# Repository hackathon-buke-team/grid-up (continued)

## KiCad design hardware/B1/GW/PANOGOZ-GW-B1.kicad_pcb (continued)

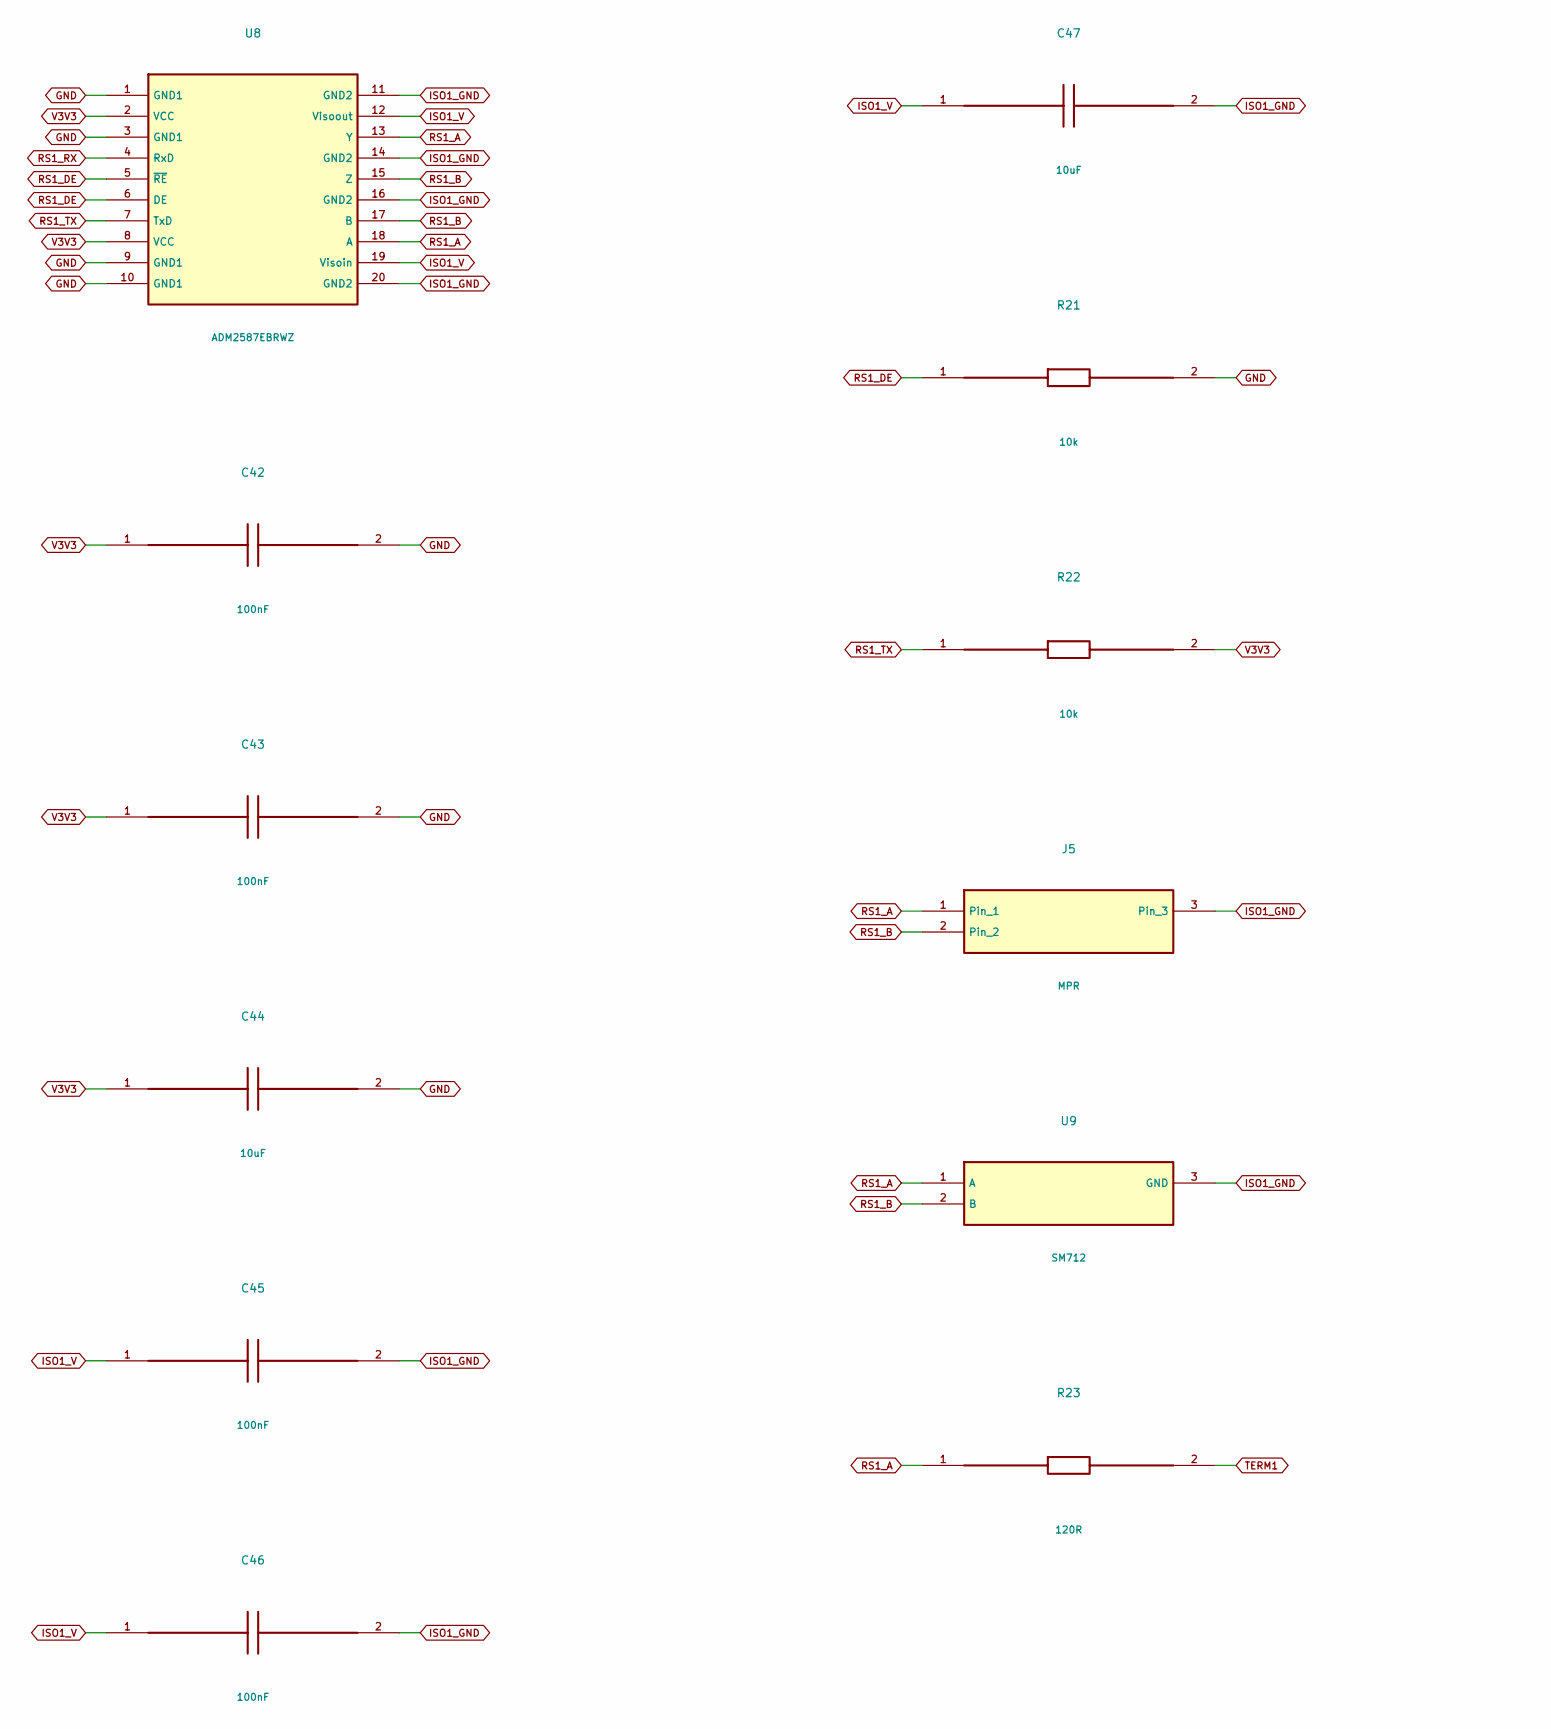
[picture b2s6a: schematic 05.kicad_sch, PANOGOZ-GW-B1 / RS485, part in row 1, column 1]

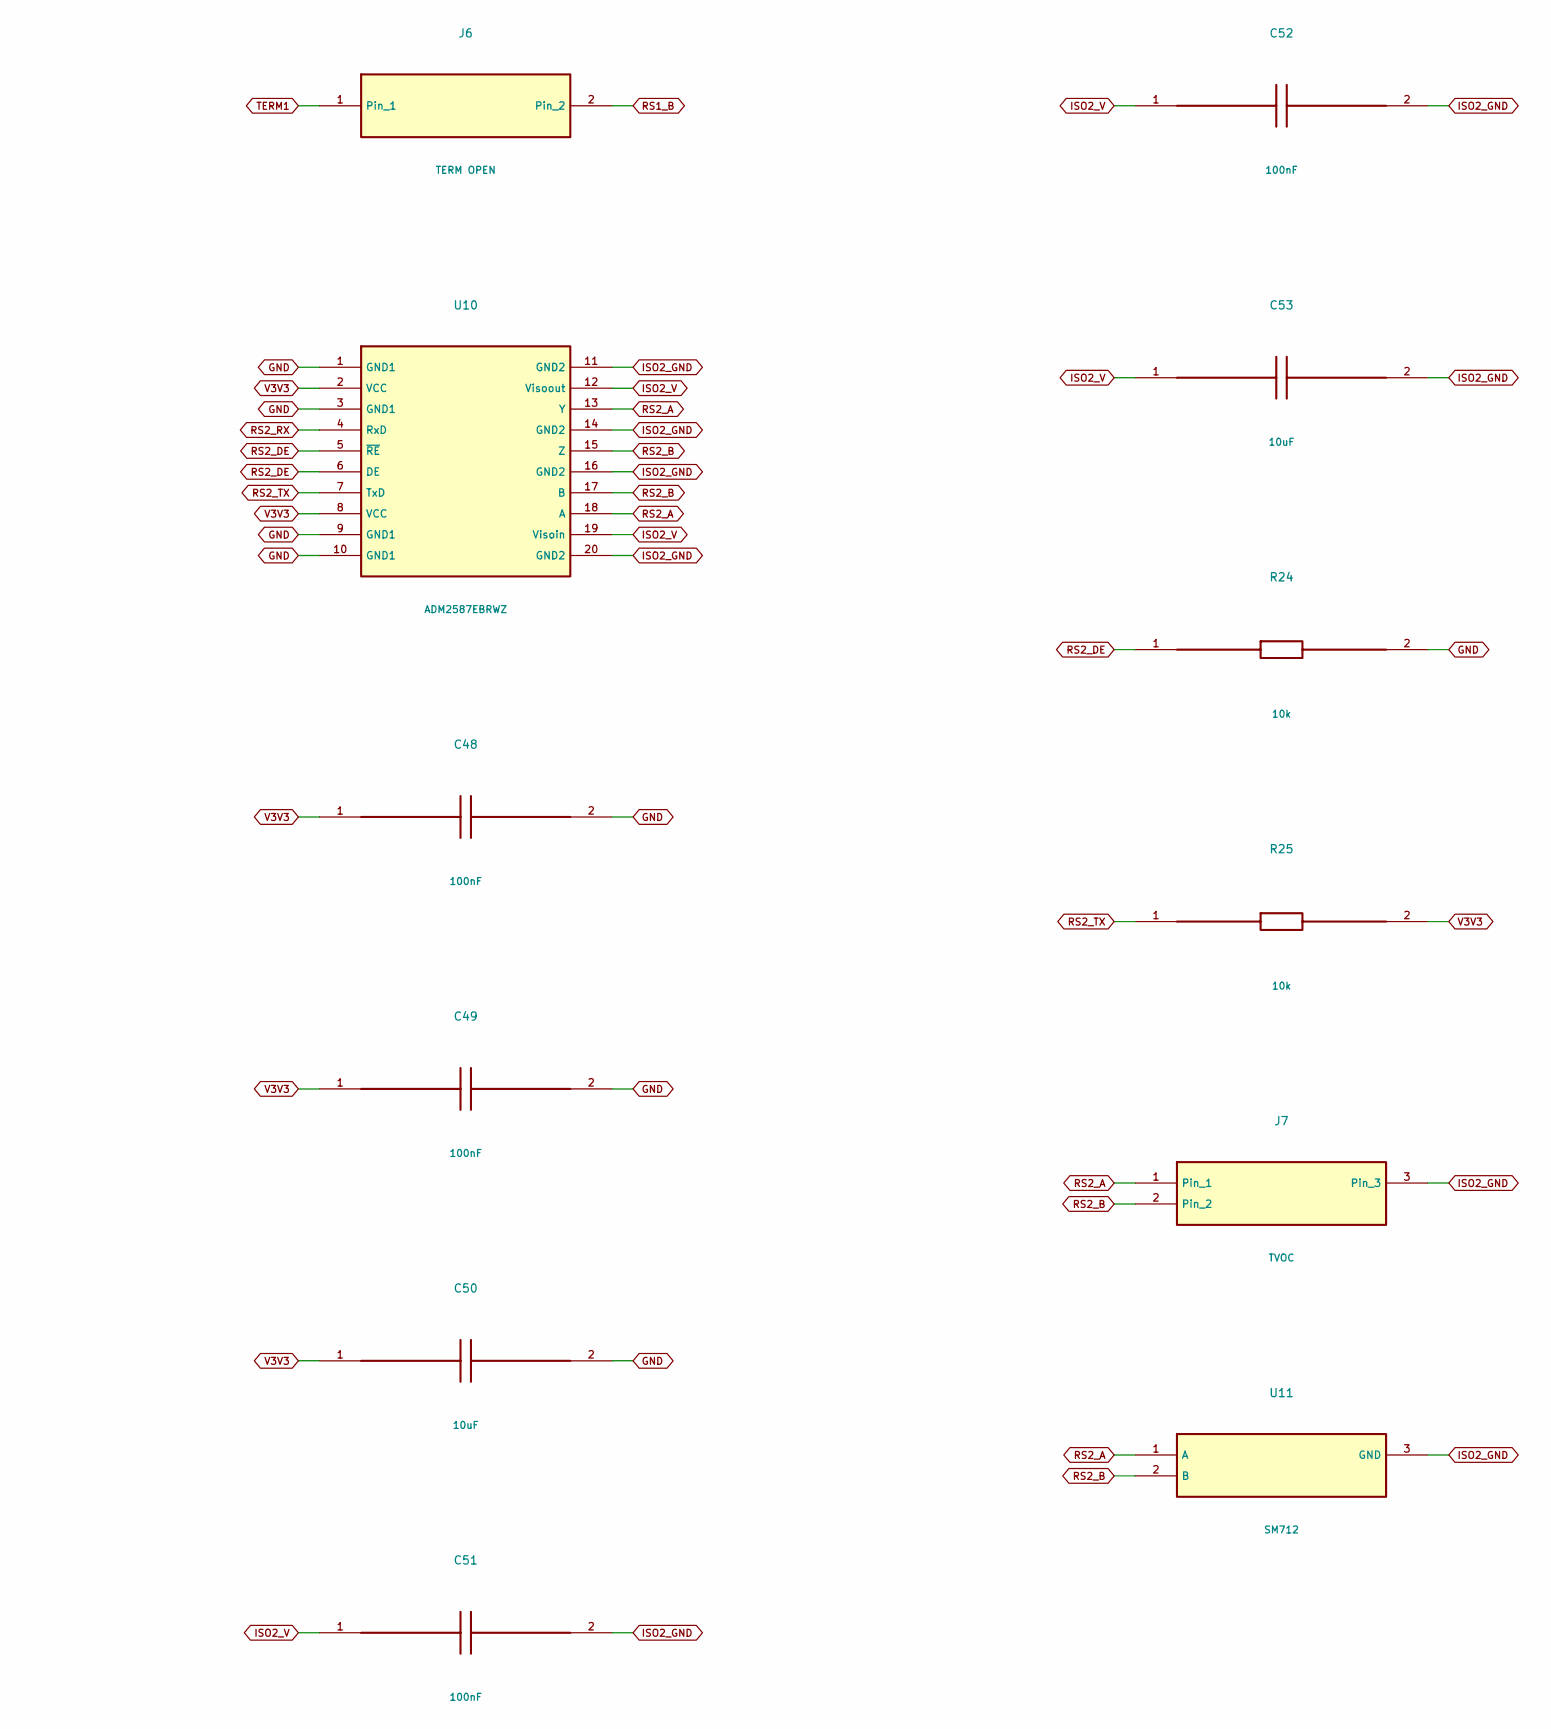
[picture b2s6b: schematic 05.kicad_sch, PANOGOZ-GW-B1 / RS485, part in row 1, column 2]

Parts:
C42, C43, C45, C46, C48, C49, C51, C52: 100nF; C_0402_1005Metric; MPN X7R 16V 100nF
C44, C47, C50, C53: 10uF; C_0805_2012Metric; MPN X7R 16V 10uF
J5: MPR; TerminalBlock_Phoenix_MKDS-1,5-3-5.08_1x03_P5.08mm_Horizont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; MPN MPR
J6: TERM OPEN; PinHeader_1x02_P2.54mm_Vertical; MPN TERM OPEN
J7: TVOC; TerminalBlock_Phoenix_MKDS-1,5-3-5.08_1x03_P5.08mm_Horizont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; MPN TVOC
R21, R22, R24, R25: 10k; R_0402_1005Metric; MPN 1% thick film 10k
R23: 120R; R_0805_2012Metric; MPN 1% thick film 120R
U8, U10: ADM2587EBRWZ; SOIC-20W_7.5x12.8mm_P1.27mm; MPN ADM2587EBRWZ
U9, U11: SM712; SOT-23; MPN SM712

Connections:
GND: C42.2, C43.2, C44.2, C48.2, C49.2, C50.2, R21.2, R24.2, U8.1 (GND1), U8.3 (GND1), U8.9 (GND1), U8.10 (GND1), U10.1 (GND1), U10.3 (GND1), U10.9 (GND1), U10.10 (GND1); also elsewhere on the board
ISO1_GND: C45.2, C46.2, C47.2, J5.3, U8.11 (GND2), U8.14 (GND2), U8.16 (GND2), U8.20 (GND2), U9.3 (GND)
ISO1_V: C45.1, C46.1, C47.1, U8.12 (Visoout), U8.19 (Visoin)
ISO2_GND: C51.2, C52.2, C53.2, J7.3, U10.11 (GND2), U10.14 (GND2), U10.16 (GND2), U10.20 (GND2), U11.3 (GND)
ISO2_V: C51.1, C52.1, C53.1, U10.12 (Visoout), U10.19 (Visoin)
RS1_A: J5.1, R23.1, U8.13 (Y), U8.18 (A), U9.1 (A)
RS1_B: J5.2, J6.2, U8.15 (Z), U8.17 (B), U9.2 (B)
RS1_DE: R21.1, U8.5 (~RE), U8.6 (DE); also elsewhere on the board
RS1_RX: U8.4 (RxD); also elsewhere on the board
RS1_TX: R22.1, U8.7 (TxD); also elsewhere on the board
RS2_A: J7.1, U10.13 (Y), U10.18 (A), U11.1 (A); also elsewhere on the board
RS2_B: J7.2, U10.15 (Z), U10.17 (B), U11.2 (B); also elsewhere on the board
RS2_DE: R24.1, U10.5 (~RE), U10.6 (DE); also elsewhere on the board
RS2_RX: U10.4 (RxD); also elsewhere on the board
RS2_TX: R25.1, U10.7 (TxD); also elsewhere on the board
TERM1: J6.1, R23.2
V3V3: C42.1, C43.1, C44.1, C48.1, C49.1, C50.1, R22.2, R25.2, U8.2 (VCC), U8.8 (VCC), U10.2 (VCC), U10.8 (VCC); also elsewhere on the board

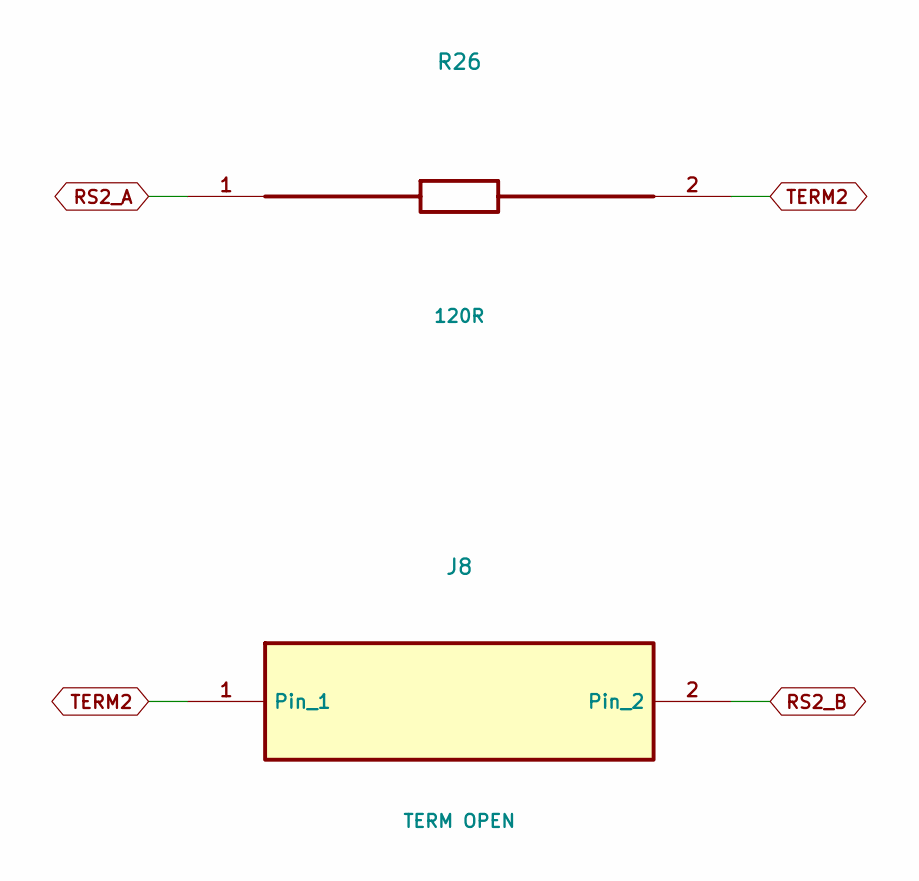
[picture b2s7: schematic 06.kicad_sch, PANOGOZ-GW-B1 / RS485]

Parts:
J8: TERM OPEN; PinHeader_1x02_P2.54mm_Vertical; MPN TERM OPEN
R26: 120R; R_0805_2012Metric; MPN 1% thick film 120R

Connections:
RS2_A: R26.1; also elsewhere on the board
RS2_B: J8.2; also elsewhere on the board
TERM2: J8.1, R26.2

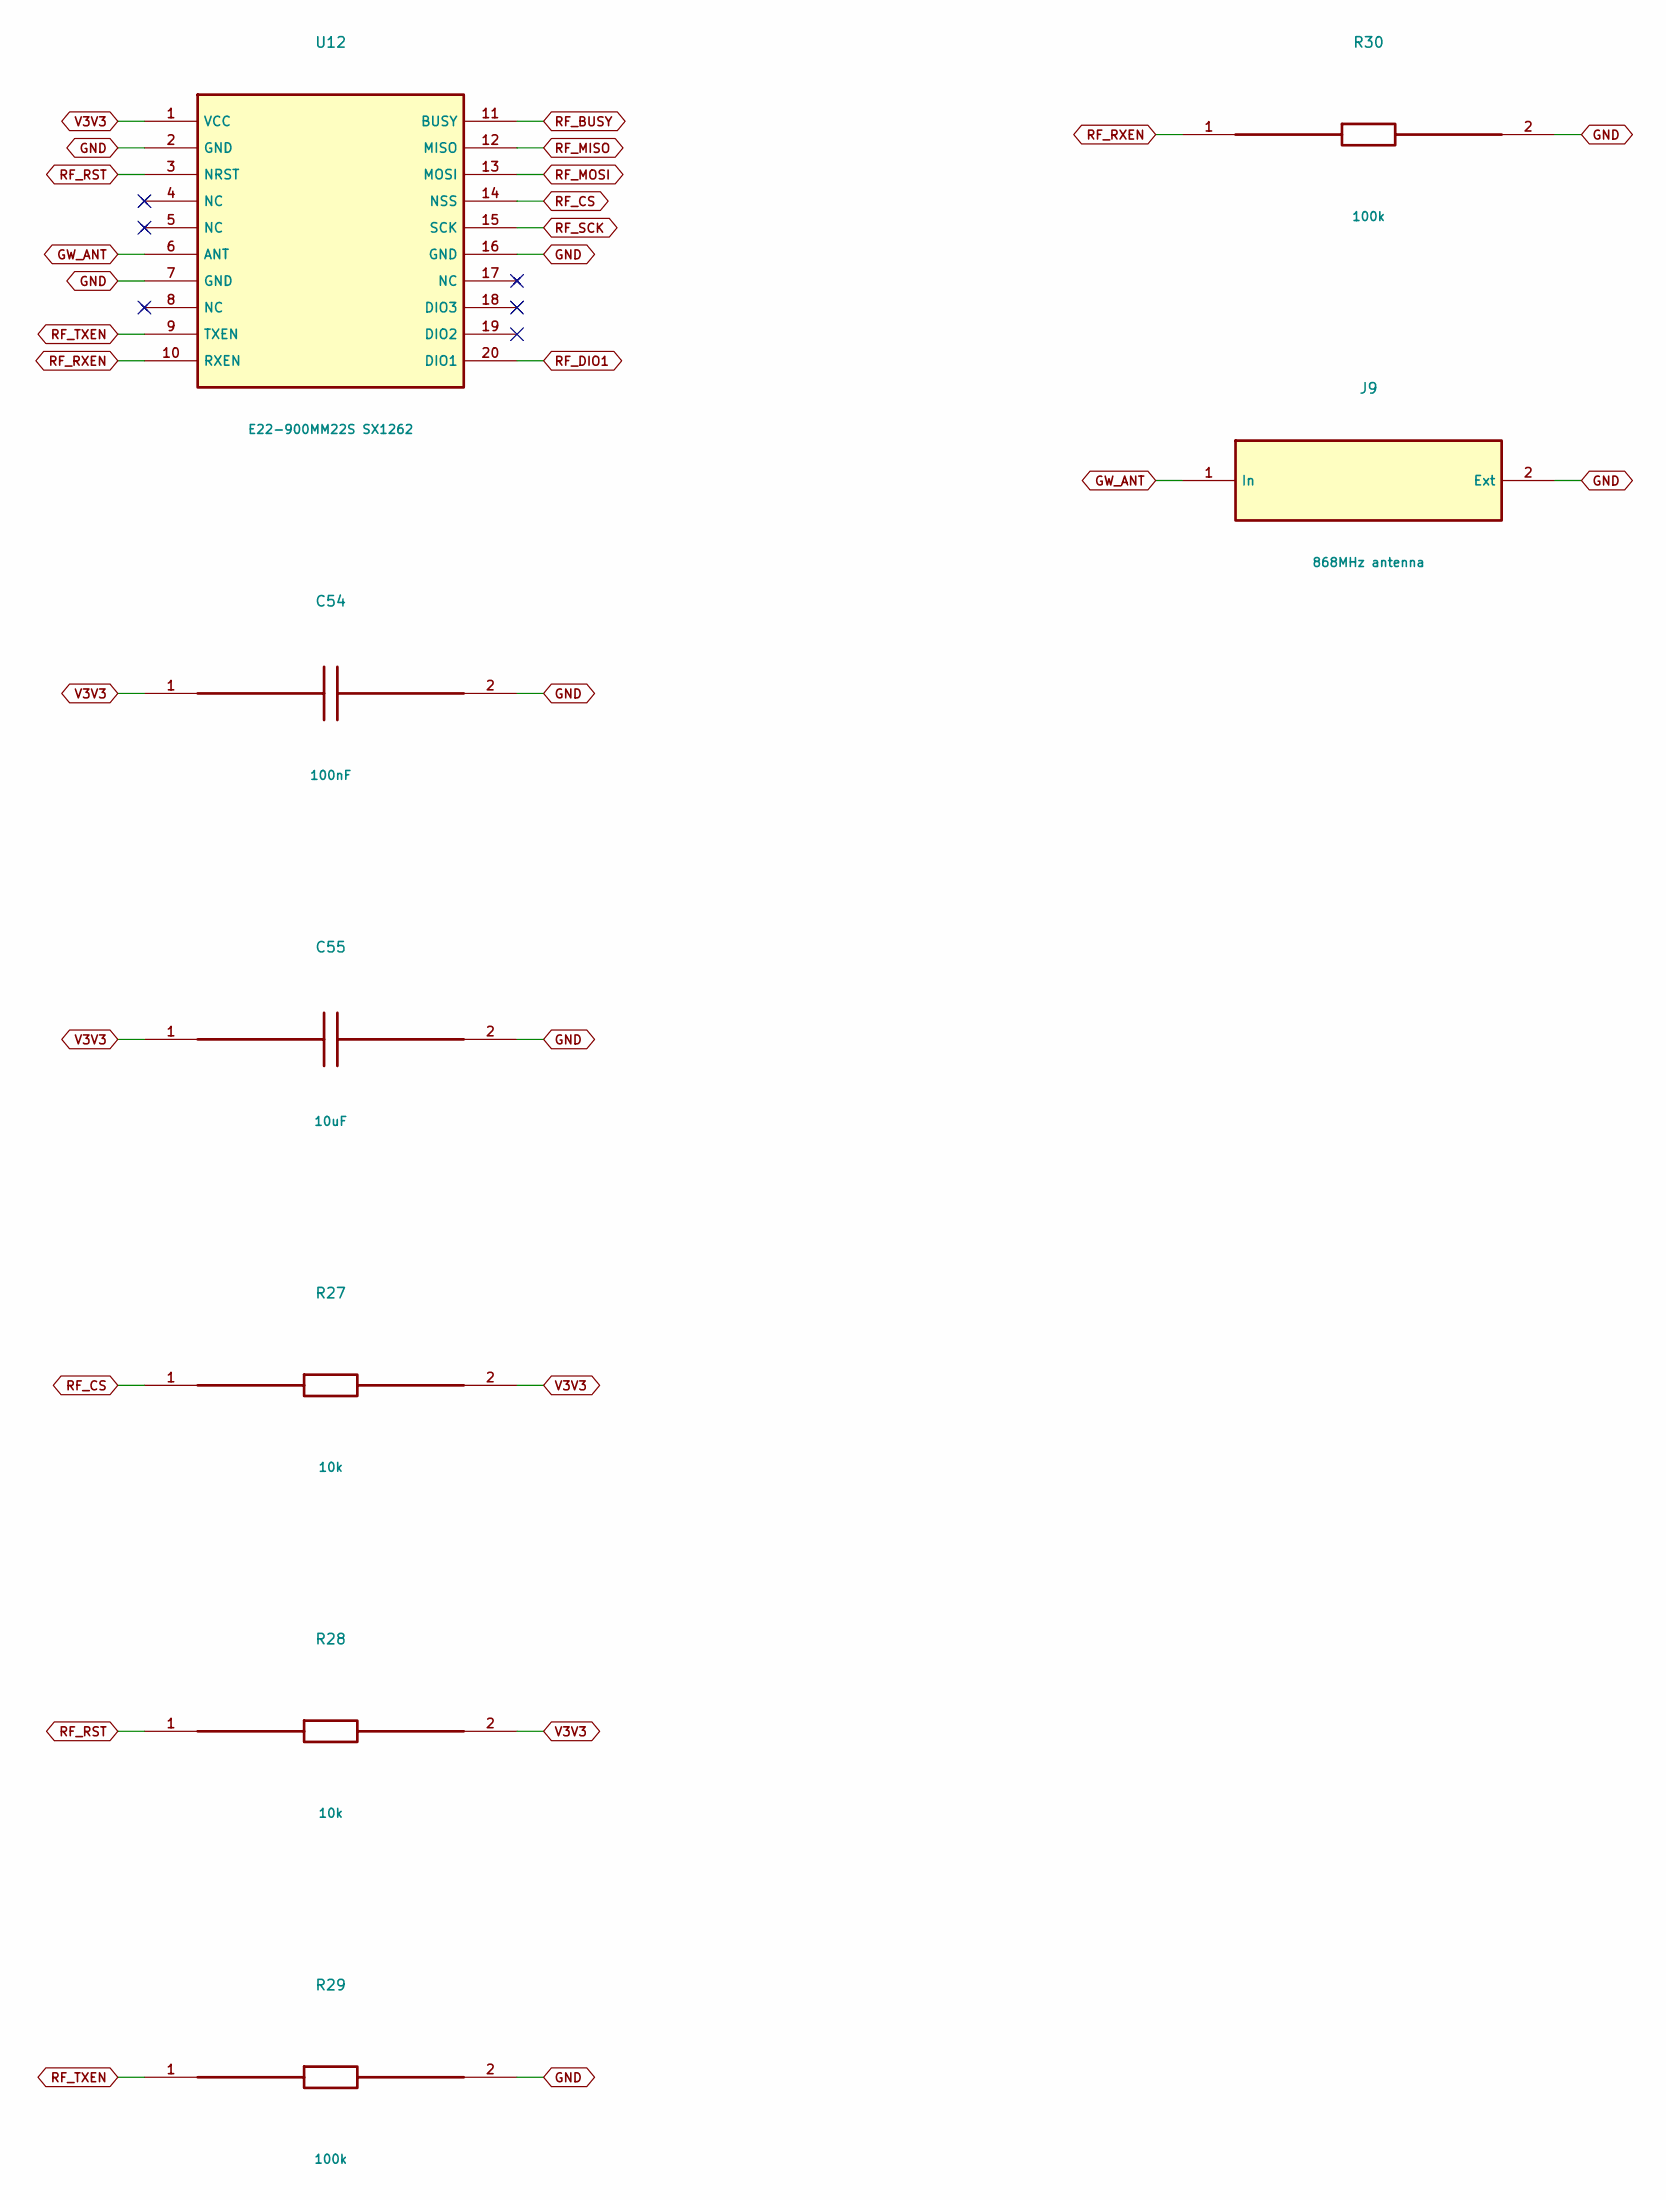
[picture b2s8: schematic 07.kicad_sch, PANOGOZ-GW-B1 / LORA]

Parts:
C54: 100nF; C_0402_1005Metric; MPN X7R 16V 100nF
C55: 10uF; C_0805_2012Metric; MPN X7R 16V 10uF
J9: 868MHz antenna; U.FL_Hirose_U.FL-R-SMT-1_Vertical; MPN 868MHz antenna
R27, R28: 10k; R_0402_1005Metric; MPN 1% thick film 10k
R29, R30: 100k; R_0402_1005Metric; MPN 1% thick film 100k
U12: E22-900MM22S SX1262; E22-900MM22S; MPN E22-900MM22S

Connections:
GND: C54.2, C55.2, J9.2 (Ext), R29.2, R30.2, U12.2 (GND), U12.7 (GND), U12.16 (GND); also elsewhere on the board
GW_ANT: J9.1 (In), U12.6 (ANT)
RF_BUSY: U12.11 (BUSY); also elsewhere on the board
RF_CS: R27.1, U12.14 (NSS); also elsewhere on the board
RF_DIO1: U12.20 (DIO1); also elsewhere on the board
RF_MISO: U12.12 (MISO); also elsewhere on the board
RF_MOSI: U12.13 (MOSI); also elsewhere on the board
RF_RST: R28.1, U12.3 (NRST); also elsewhere on the board
RF_RXEN: R30.1, U12.10 (RXEN); also elsewhere on the board
RF_SCK: U12.15 (SCK); also elsewhere on the board
RF_TXEN: R29.1, U12.9 (TXEN); also elsewhere on the board
V3V3: C54.1, C55.1, R27.2, R28.2, U12.1 (VCC); also elsewhere on the board

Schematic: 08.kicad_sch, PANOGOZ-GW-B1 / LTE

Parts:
J10: SIM connector; PinHeader_1x06_P2.00mm_Vertical; MPN SIM connector
U13: EC21-E MiniPCIe SOCKET; TE_2041119_1; MPN 2041119-1

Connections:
GND: J10.4, U13.4 (PIN_4), U13.9 (PIN_9), U13.15 (PIN_15), U13.18 (PIN_18), U13.21 (PIN_21), U13.26 (PIN_26), U13.27 (PIN_27), U13.29 (PIN_29), U13.34 (PIN_34), U13.35 (PIN_35), U13.37 (PIN_37), U13.40 (PIN_40), U13.43 (PIN_43), U13.50 (PIN_50); also elsewhere on the board
LTE_3V3: U13.2 (PIN_2), U13.39 (PIN_39), U13.41 (PIN_41), U13.52 (PIN_52); also elsewhere on the board
LTE_RX: U13.13 (PIN_13); also elsewhere on the board
LTE_TX: U13.11 (PIN_11); also elsewhere on the board
SIM_CLK: J10.3, U13.12 (PIN_12)
SIM_IO: J10.5, U13.10 (PIN_10)
SIM_RST: J10.2, U13.14 (PIN_14)
SIM_VDD: J10.1, U13.8 (PIN_8)
USB_DM: U13.36 (PIN_36); also elsewhere on the board
USB_DP: U13.38 (PIN_38); also elsewhere on the board

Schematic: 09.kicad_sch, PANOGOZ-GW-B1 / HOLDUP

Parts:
C56: 22uF; C_0805_2012Metric; MPN X7R 16V 22uF
C57: 10nF; C_0402_1005Metric; MPN X7R 16V 10nF
D1, D2: SS34; D_SMA; MPN SS34
D3: BAT54; D_SOD-123; MPN BAT54
J11: 2x10F 2.7V EDLC pack; JST_SH_SM03B-SRSS-TB_1x03-1MP_P1.00mm_Horizontal; MPN 2x10F 2.7V EDLC pack
R31: 100R 1W; R_2512_6332Metric; MPN 1% thick film 100R 1W
R32, R33: 10k; R_0402_1005Metric; MPN 1% thick film 10k
R34, R35: 100k; R_0402_1005Metric; MPN 1% thick film 100k

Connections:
GND: C56.2, C57.2, J11.3, R33.2, R35.2; also elsewhere on the board
PFAIL_ADC: C57.1, R34.2, R35.1; also elsewhere on the board
SC_CHARGE: D3.1 (K), R31.1
SC_MID: J11.2, R32.2, R33.1
SC_TOP: D2.2 (A), J11.1, R31.2, R32.1
V5: D1.2 (A), D3.2 (A), R34.1; also elsewhere on the board
V5_HOLD: C56.1, D1.1 (K), D2.1 (K); also elsewhere on the board

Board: 4 copper layers, 126 parts (1 on the bottom side), 92 nets, no tracks yet.

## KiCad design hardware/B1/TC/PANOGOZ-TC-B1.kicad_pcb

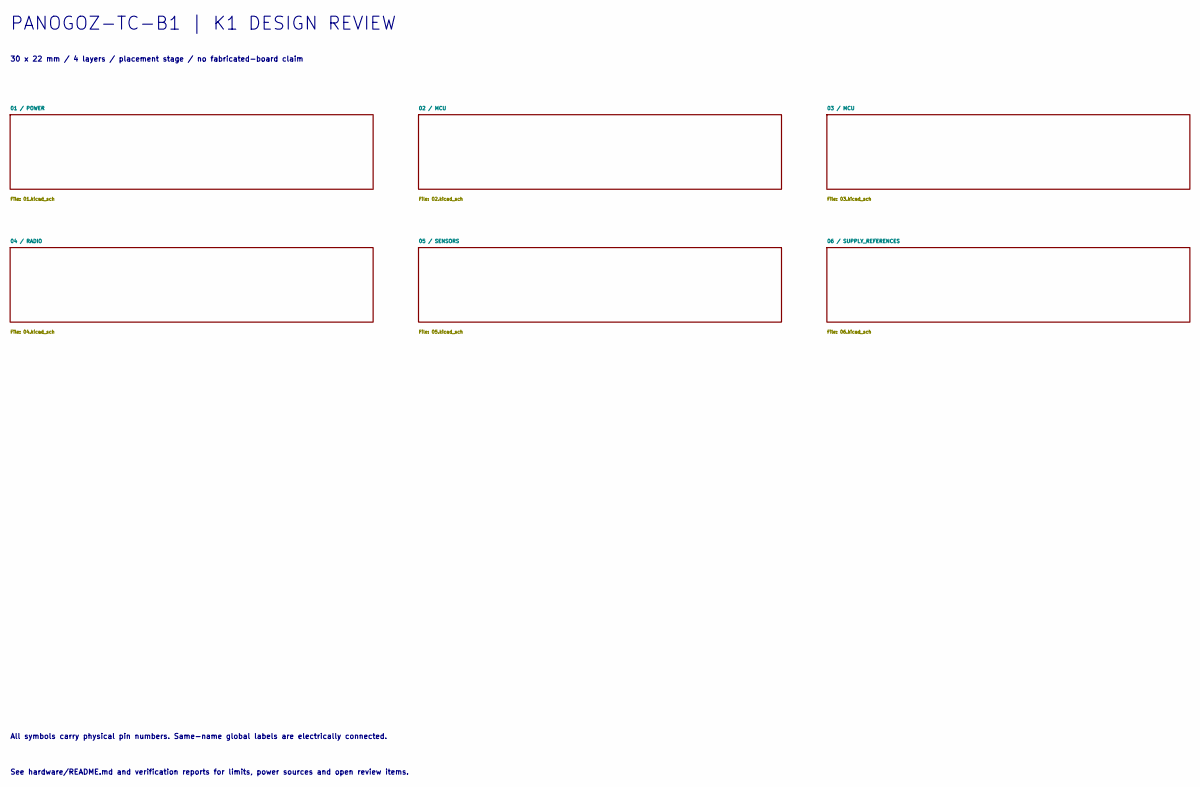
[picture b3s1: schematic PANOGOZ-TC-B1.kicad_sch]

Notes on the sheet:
PANOGOZ-TC-B1 | K1 DESIGN REVIEW
30 x 22 mm / 4 layers / placement stage / no fabricated-board claim
All symbols carry physical pin numbers. Same-name global labels are electrically connected.
See hardware/README.md and verification reports for limits, power sources and open review items.

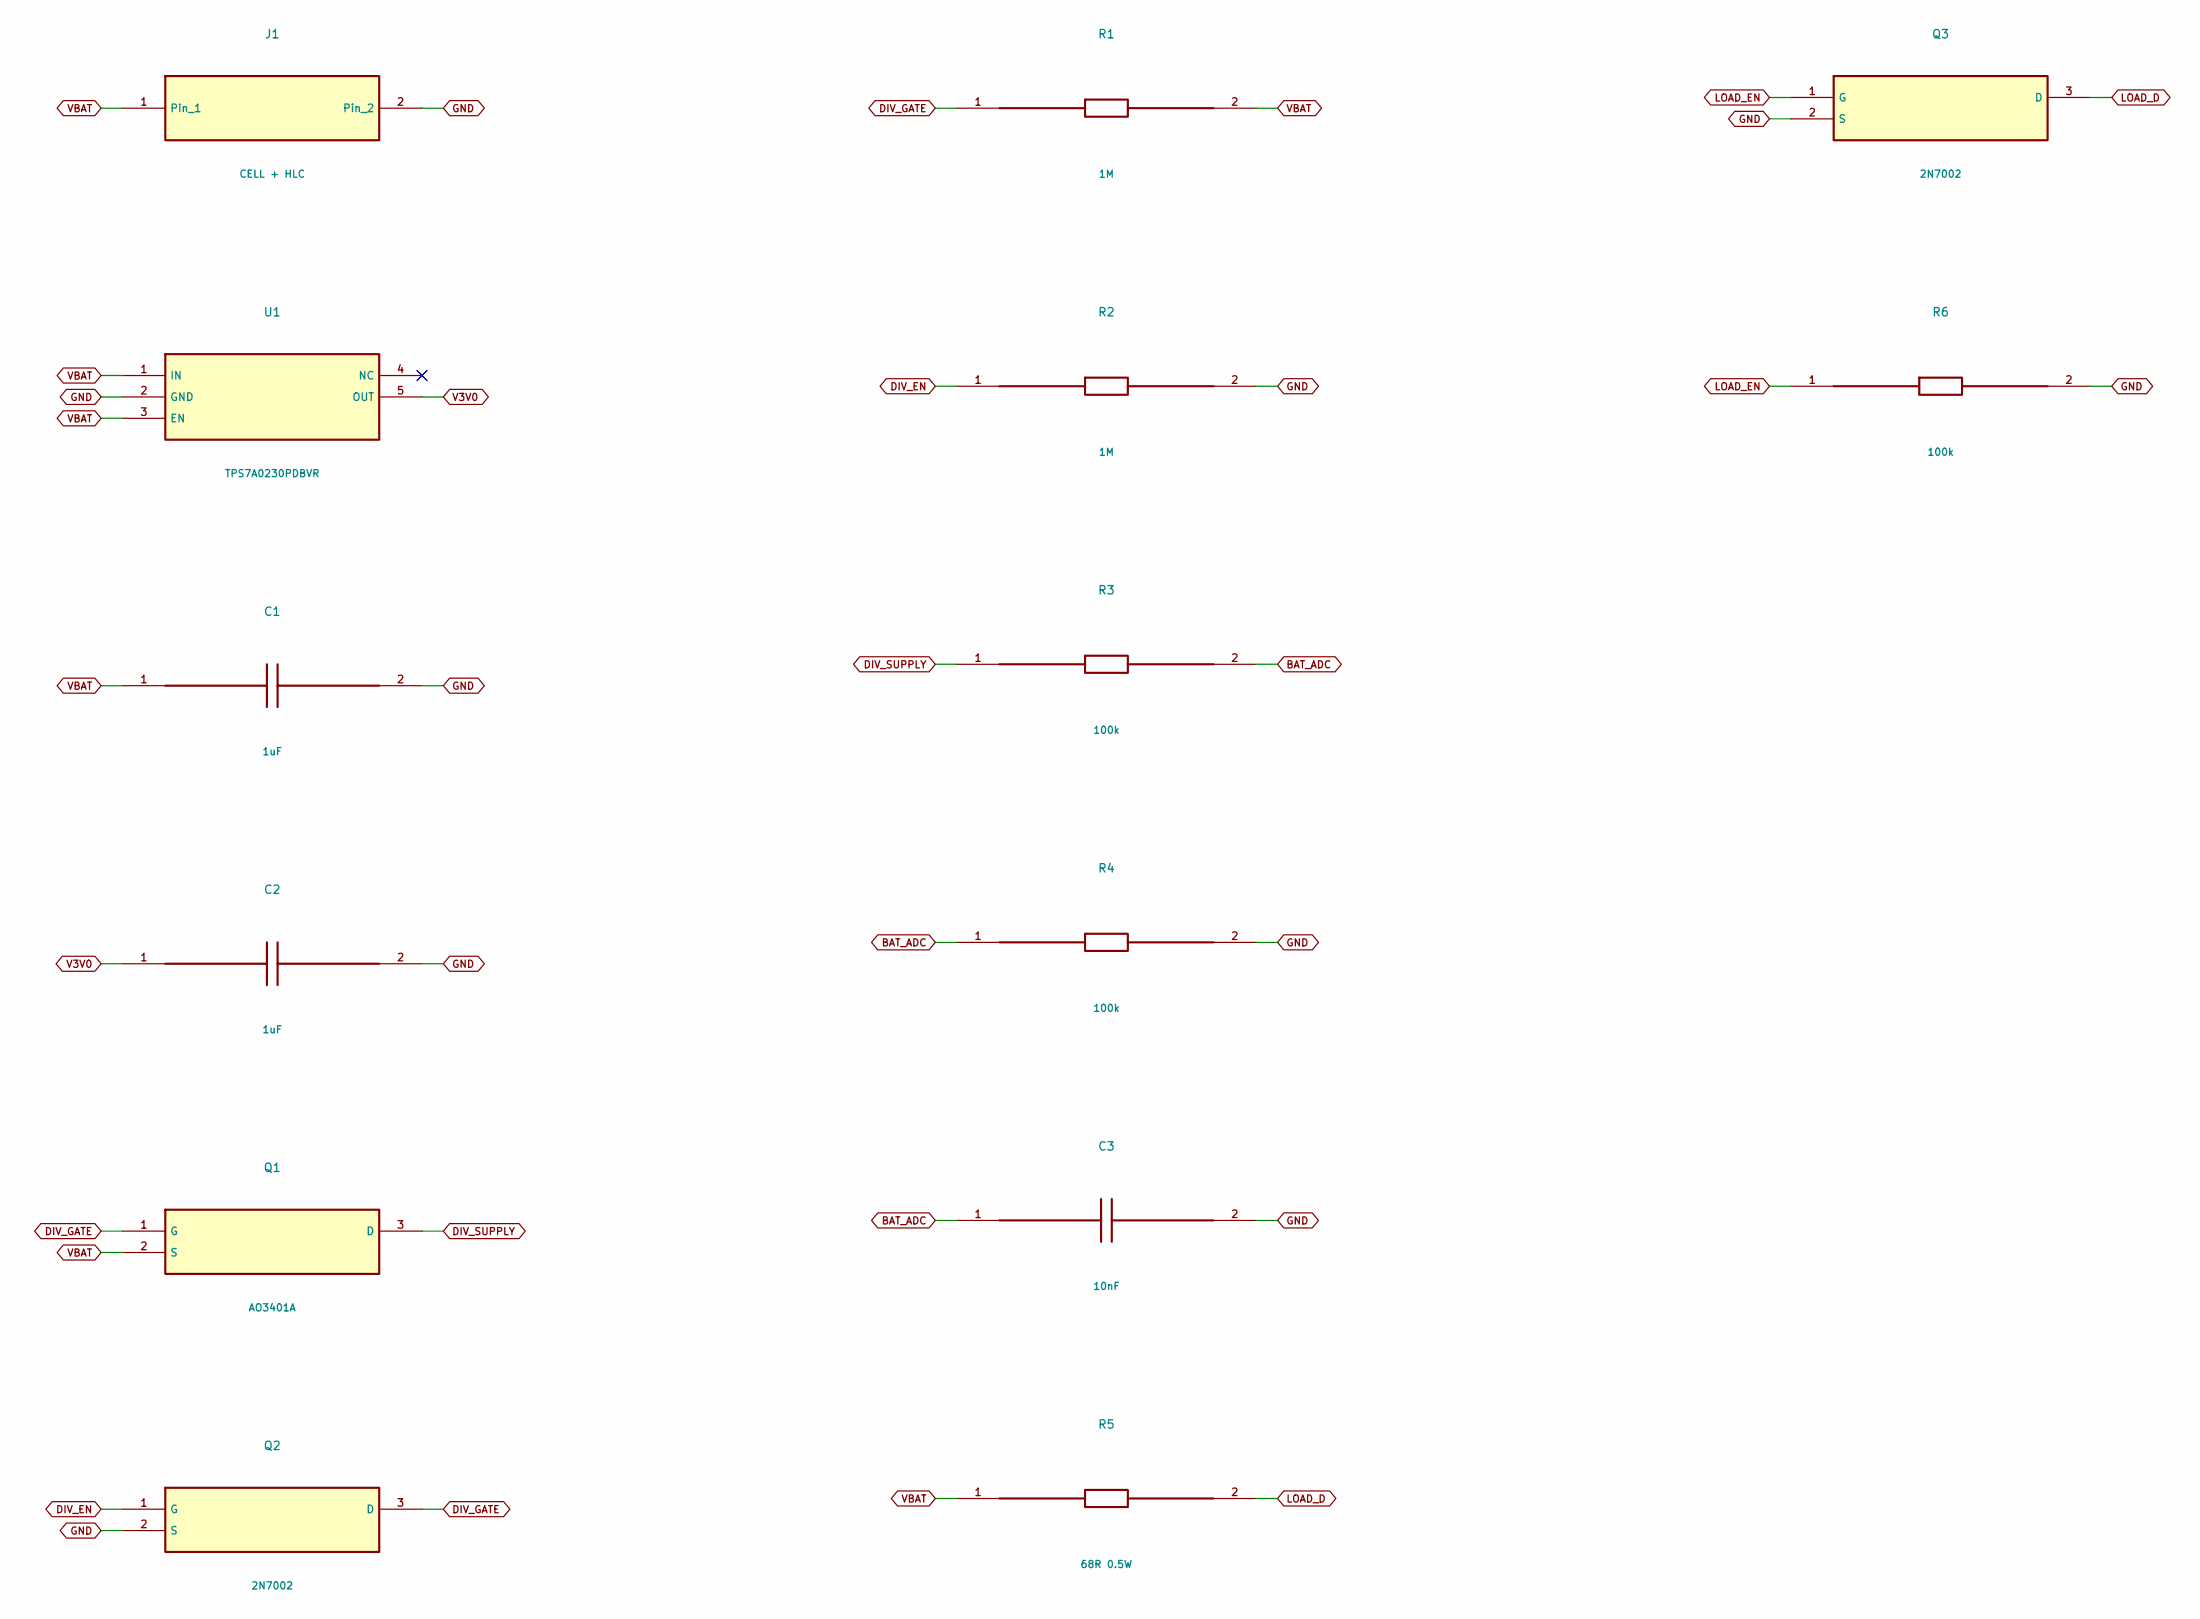
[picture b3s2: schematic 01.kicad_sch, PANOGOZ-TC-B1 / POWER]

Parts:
C1, C2: 1uF; C_0402_1005Metric; MPN X7R 16V 1uF
C3: 10nF; C_0402_1005Metric; MPN X7R 16V 10nF
J1: CELL + HLC; JST_SH_SM02B-SRSS-TB_1x02-1MP_P1.00mm_Horizontal; MPN CELL + HLC
Q1: AO3401A; SOT-23; MPN AO3401A
Q2, Q3: 2N7002; SOT-23; MPN 2N7002
R1, R2: 1M; R_0402_1005Metric; MPN 1% thick film 1M
R3, R4, R6: 100k; R_0402_1005Metric; MPN 1% thick film 100k
R5: 68R 0.5W; R_1210_3225Metric; MPN 1% thick film 68R 0.5W
U1: TPS7A0230PDBVR; SOT-23-5; MPN TPS7A0230PDBVR

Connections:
BAT_ADC: C3.1, R3.2, R4.1; also elsewhere on the board
DIV_EN: Q2.1 (G), R2.1; also elsewhere on the board
DIV_GATE: Q1.1 (G), Q2.3 (D), R1.1
DIV_SUPPLY: Q1.3 (D), R3.1
GND: C1.2, C2.2, C3.2, J1.2, Q2.2 (S), Q3.2 (S), R2.2, R4.2, R6.2, U1.2 (GND); also elsewhere on the board
LOAD_D: Q3.3 (D), R5.2
LOAD_EN: Q3.1 (G), R6.1; also elsewhere on the board
V3V0: C2.1, U1.5 (OUT); also elsewhere on the board
VBAT: C1.1, J1.1, Q1.2 (S), R1.2, R5.1, U1.1 (IN), U1.3 (EN)
